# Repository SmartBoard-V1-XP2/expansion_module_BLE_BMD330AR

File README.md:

# Expansion odule : BLE BMD330AR

## Overview
This repository hosts the design and implementation of the BLE BMD330AR Expansion Module. The module integrates the BMD-330-A-R, a Bluetooth 5.0 Low Energy module, suitable for a wide range of IoT and automation applications. It connects to the smartboard via a single slot, utilizing four serial port lines: RX, TX, RTS, and CTS, along with two configuration pins.

## Key Features of BMD-330
- **Bluetooth 5.0 Low Energy** for efficient wireless communication.
- **200m Range**: Extensive coverage for various applications.
- **Low Power Consumption**: Under 15.4 mA in Tx mode and less than 10 mA in Rx mode.
- **Multiple Interfaces**: SPI, UART, I2C, GPIO, PWM, and PDM.
- **Compact Size**: Measures 14 x 9.8 x 1.9 mm, ideal for embedded solutions.

## Contributions and Feedback
Contributions to this project are welcome. If you have suggestions for improvement or have developed additional features, please fork the repository, make your changes, and submit a pull request. For any questions or issues, please open an issue in the GitHub repository.

## License
This charger project is licensed under the MIT License with the following terms:

- **Permission to Use**: You are free to use, modify, and distribute this charger design in both private and commercial settings.
- **Attribution Requirement**: While not required, attribution to the original author, Adam Łuczak, is appreciated. This can be done through a citation or a link back to this repository.
- **No Warranty**: This design is provided "as is", without warranty of any kind. Use it at your own risk.
- **Liability**: The author is not liable for any damages or losses that may arise from the use of this design.

For the full terms and conditions, please refer to the MIT License documentation.

## Contact
Should you have any inquiries or suggestions regarding this charger project, please don't hesitate to contact Adam Łuczak at adam.luczak@outlook.com.

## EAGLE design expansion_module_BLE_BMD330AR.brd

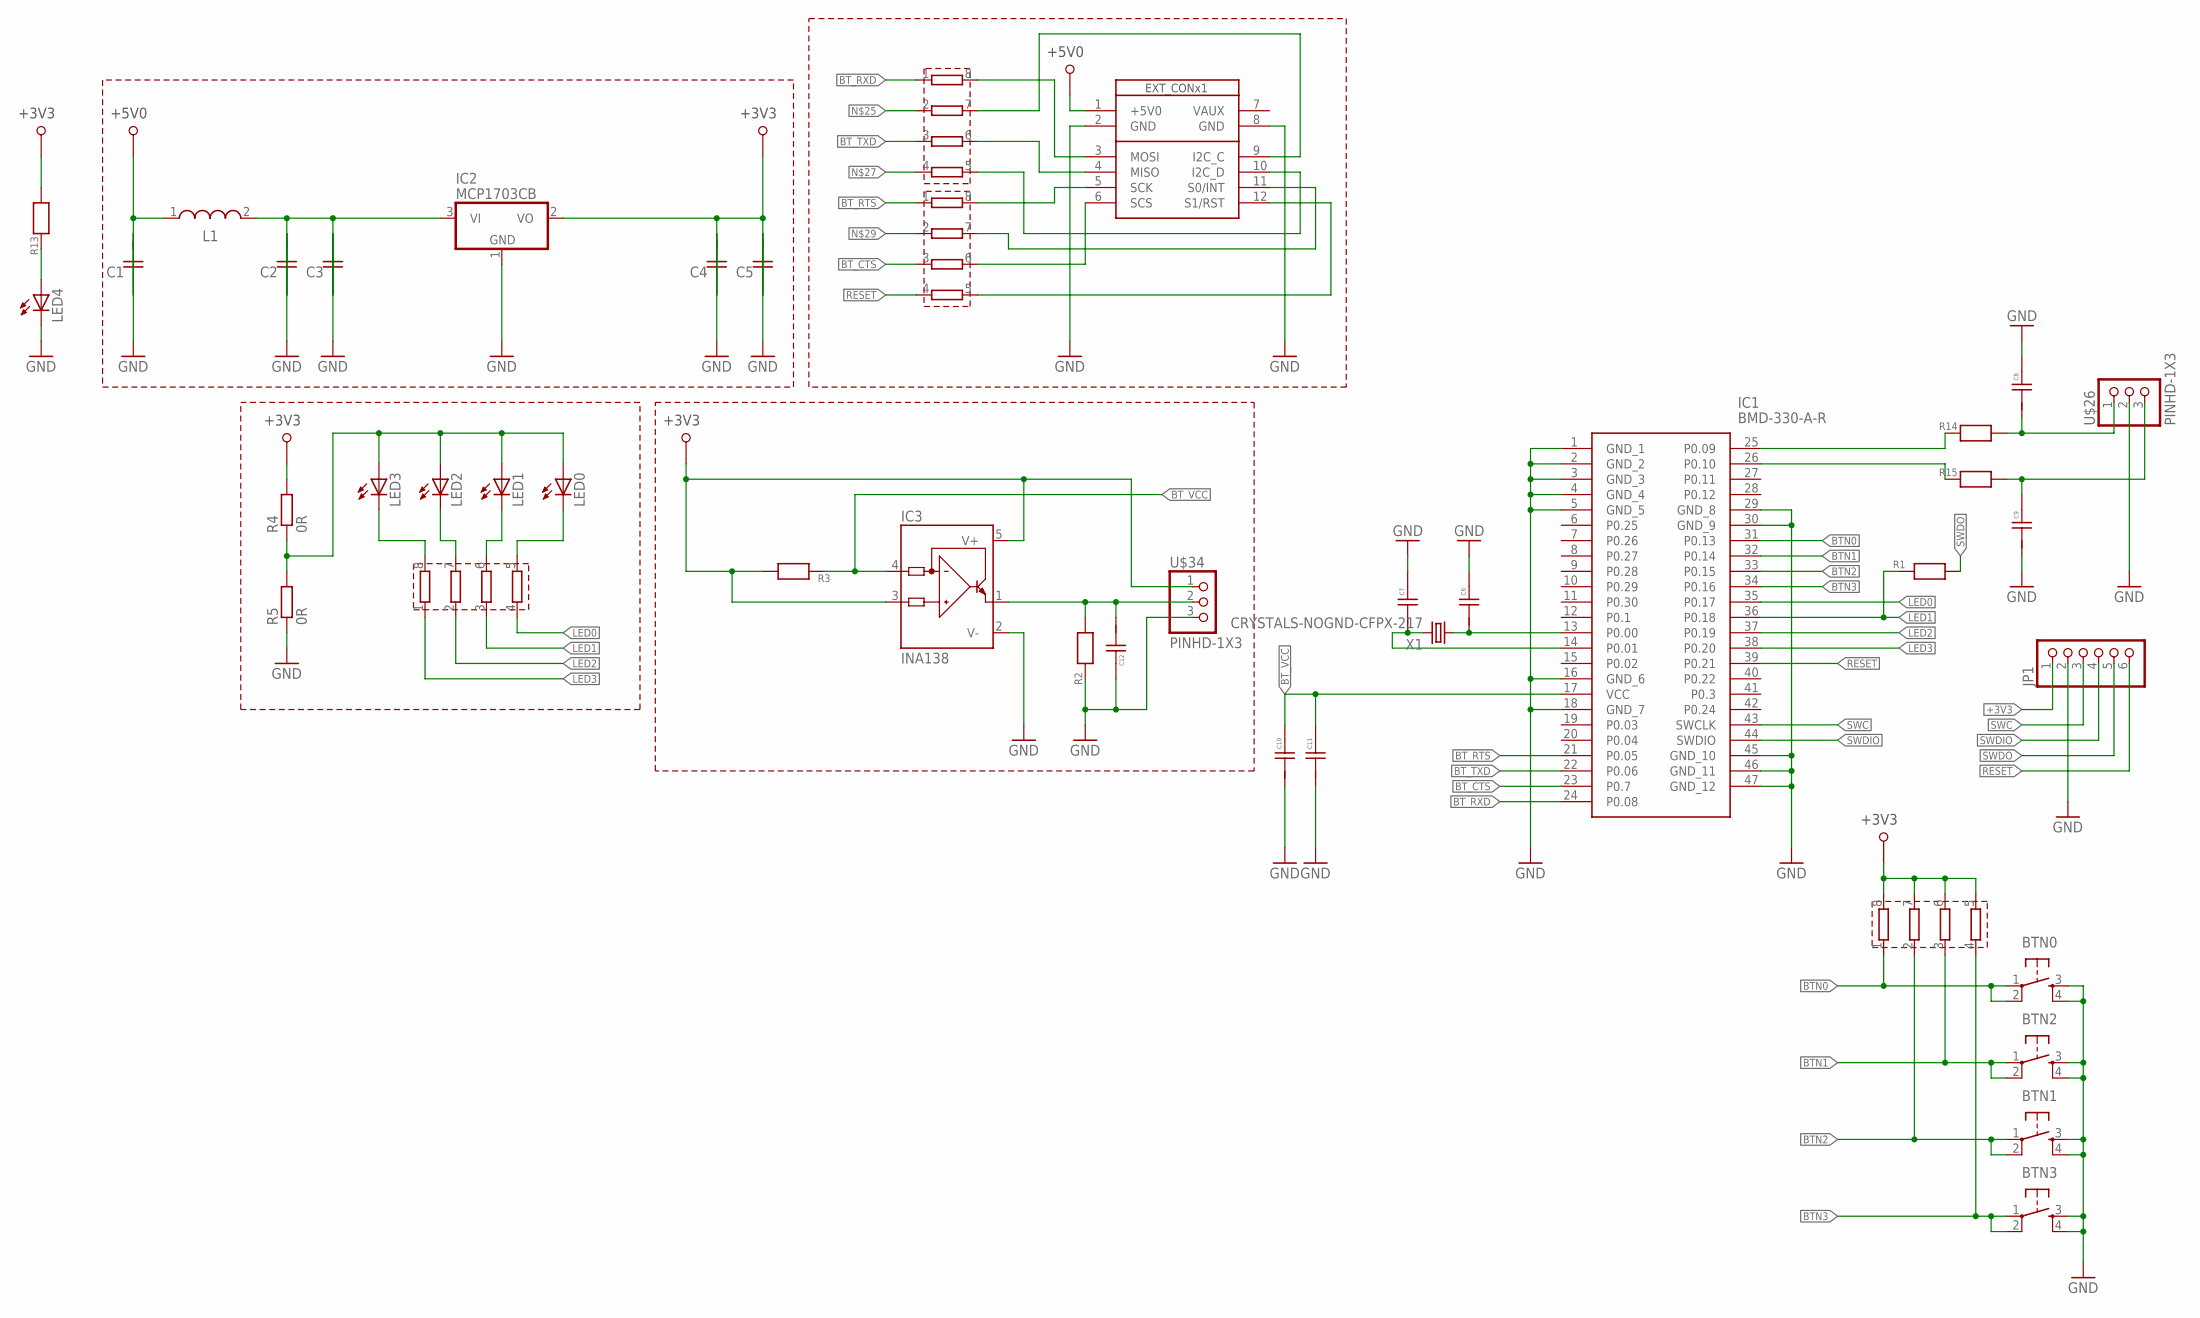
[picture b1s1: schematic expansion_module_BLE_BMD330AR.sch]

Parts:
BTN0, BTN1, BTN2, BTN3: TACT-SWITCH-SMD_KMR2; KMR2
C1, C2, C3, C4, C5, C6, C7, C8, C9, C10, C11, C12: CAPACITOR_CERAMIC_0402; CAPACITOR_0402
IC1: BMD-330-A-R; BMD-300
IC2: MCP1703CB; SOT23
IC3: INA138; SOT23-5
JP1: PINHD-1X6; 1X06
L1: WE-LQ_1210; WE-LQ_M
LED0, LED1, LED2, LED3: LEDSML0603; SML0603
LED4: LED_ESML0603; LED_SML0603
R1, R2, R3, R13, R14, R15: RESISTOR_0402; RESISITOR_0402
R4, R5: 0R; R0603
RN1, RN2, RN3, RN4: RESISTOR-DIL_4R-N; EXB28V
U$1: SB_EXT_CON_X1_SPI; SB_EXT_CON_X1_FULL
U$26, U$34: PINHD-1X3; 1X03
X1: CRYSTALS-NOGND-CFPX-217; 3.2X1.5-2-PAD

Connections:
+3V3: C4.2, C5.2, IC2.2 (VO), IC3.3 (IN+), IC3.5 (V+), JP1.1, R3.2, R4.2, R13.2, RN4.5, RN4.6, RN4.7, RN4.8, U$34.1
+5V0: C1.2, L1.1, U$1.1 (+5V0)
BTN0: BTN0.1, BTN0.2, IC1.31 (P0.13), RN4.1
BTN1: BTN2.1, BTN2.2, IC1.32 (P0.14), RN4.3
BTN2: BTN1.1, BTN1.2, IC1.33 (P0.15), RN4.2
BTN3: BTN3.1, BTN3.2, IC1.34 (P0.16), RN4.4
BT_CTS: IC1.23 (P0.7), RN1.3
BT_RTS: IC1.21 (P0.05), RN1.1
BT_RXD: IC1.24 (P0.08), RN2.1
BT_TXD: IC1.22 (P0.06), RN2.3
BT_VCC: C10.2, C11.2, IC1.17 (VCC), IC3.4 (IN-), R3.1
GND: BTN0.3, BTN0.4, BTN1.3, BTN1.4, BTN2.3, BTN2.4, BTN3.3, BTN3.4, C1.1, C2.1, C3.1, C4.1, C5.1, C6.2, C7.2, C8.2, C9.1, C10.1, C11.1, C12.2, IC1.1 (GND_1), IC1.2 (GND_2), IC1.3 (GND_3), IC1.4 (GND_4), IC1.5 (GND_5), IC1.16 (GND_6), IC1.18 (GND_7), IC1.29 (GND_8), IC1.30 (GND_9), IC1.45 (GND_10), IC1.46 (GND_11), IC1.47 (GND_12), IC2.1 (GND), IC3.2 (V-), JP1.2, LED4.C, R2.1, R5.1, U$1.2 (GND), U$1.8 (GND), U$26.2, U$34.3
LED0: IC1.35 (P0.17), RN3.4
LED1: IC1.36 (P0.18), R1.1, RN3.3
LED2: IC1.37 (P0.19), RN3.2
LED3: IC1.38 (P0.20), RN3.1
unnamed: C2.2, C3.2, IC2.3 (VI), L1.2
unnamed: LED2.C, RN3.7
unnamed: LED1.C, RN3.6
unnamed: RN2.6, U$1.4 (MISO)
unnamed: LED0.A, LED1.A, LED2.A, LED3.A, R4.1, R5.2
unnamed: LED0.C, RN3.5
unnamed: LED4.A, R13.1
unnamed: RN2.8, U$1.3 (MOSI)
unnamed: RN1.8, U$1.5 (SCK)
unnamed: RN1.6, U$1.6 (SCS)
unnamed: RN2.7, U$1.9 (I2C_C)
unnamed: C12.1, IC3.1 (OUT), R2.2, U$34.2
unnamed: IC1.25 (P0.09), R14.1
unnamed: IC1.26 (P0.10), R15.1
unnamed: C9.2, R15.2, U$26.3
unnamed: C8.1, R14.2, U$26.1
unnamed: RN2.5, U$1.10 (I2C_D)
unnamed: RN1.7, U$1.11 (S0/INT)
unnamed: RN1.5, U$1.12 (S1/RST)
unnamed: LED3.C, RN3.8
unnamed: C6.1, IC1.13 (P0.00), X1.1
unnamed: C7.1, IC1.14 (P0.01), X1.2
RESET: IC1.39 (P0.21), JP1.6, RN1.4
SWC: IC1.43 (SWCLK), JP1.3
SWDIO: IC1.44 (SWDIO), JP1.4
SWDO: JP1.5, R1.2

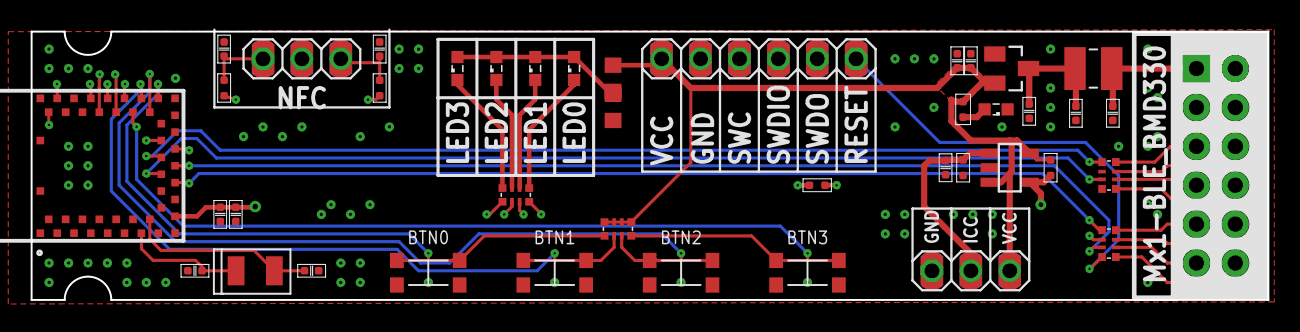
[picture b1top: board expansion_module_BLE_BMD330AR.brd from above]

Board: 4 copper layers, 80.8 x 17.5 mm, 42 parts (0 on the bottom side), 42 nets.

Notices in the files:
README.md:
License: MIT
parts and their libraries:
EagleLibrary_Wuerth_Elektronik_eiSos_rev: Copyright: Würth Elektronik
FaBo-Switch: Released under the Creative Commons Attribution-ShareAlike 4.0 License
https://creativecommons.org/licenses/by-sa/4.0
